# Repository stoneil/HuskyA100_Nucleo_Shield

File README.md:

Husky A100 Nucleo Shield
===

## Circuit

This board is for my MQP (Major Qualifying Project) to develop a autonomous robotic platform to compete in the Intelligent Ground Vehicle Competition. The purpose of this board is to provide a secure connection between the STM32F7 Nucleo microcontroller board, the Talon motor controllers (PWM) and the US Digital quadrature encoders. It breaks out power and I/O to all the connectors.

## PCB Layout
v1.0

v1.2

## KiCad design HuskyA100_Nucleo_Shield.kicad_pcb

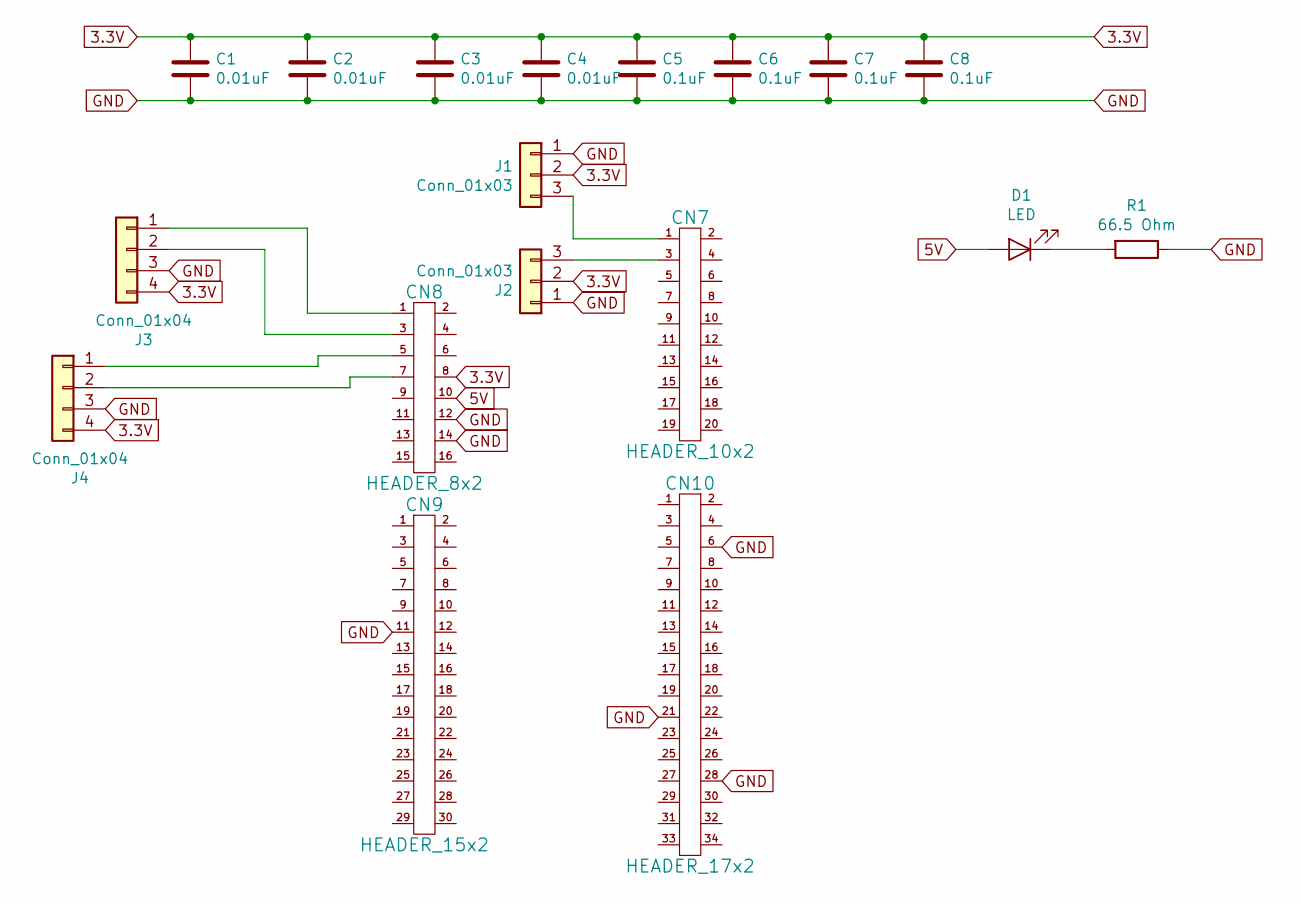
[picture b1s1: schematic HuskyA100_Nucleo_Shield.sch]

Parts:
C1, C2, C3, C4: 0.01uF; C_2220_5650Metric_Pad1.97x5.40mm_HandSolder
C5, C6, C7, C8: 0.1uF; C_2220_5650Metric_Pad1.97x5.40mm_HandSolder
CN7: HEADER_10x2; PinSocket_2x10_P2.54mm_Vertical
CN8: HEADER_8x2; PinSocket_2x08_P2.54mm_Vertical
CN9: HEADER_15x2; PinSocket_2x15_P2.54mm_Vertical
CN10: HEADER_17x2; PinSocket_2x17_P2.54mm_Vertical
D1: LED; LED_PLCC-2
J1, J2: Conn_01x03; Molex Mini-Lock Horizontal Header 3 circuit
J3, J4: Conn_01x04; Molex Mini-Lock Horizontal Header 4 circuit
R1: 66.5 Ohm; R_1206_3216Metric_Pad1.42x1.75mm_HandSolder

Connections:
3.3V: C1.1, C2.1, C3.1, C4.1, C5.1, C6.1, C7.1, C8.1, CN8.8, J1.2, J2.2, J3.4, J4.4
5V: CN8.10, D1.2 (A)
GND: C1.2, C2.2, C3.2, C4.2, C5.2, C6.2, C7.2, C8.2, CN8.12, CN8.14, CN9.11, CN10.6, CN10.21, CN10.28, J1.1, J2.1, J3.3, J4.3, R1.1
unnamed: CN7.1, J1.3
unnamed: CN7.3, J2.3
unnamed: CN8.1, J3.1
unnamed: CN8.3, J3.2
unnamed: CN8.5, J4.1
unnamed: CN8.7, J4.2
unnamed: D1.1 (K), R1.2

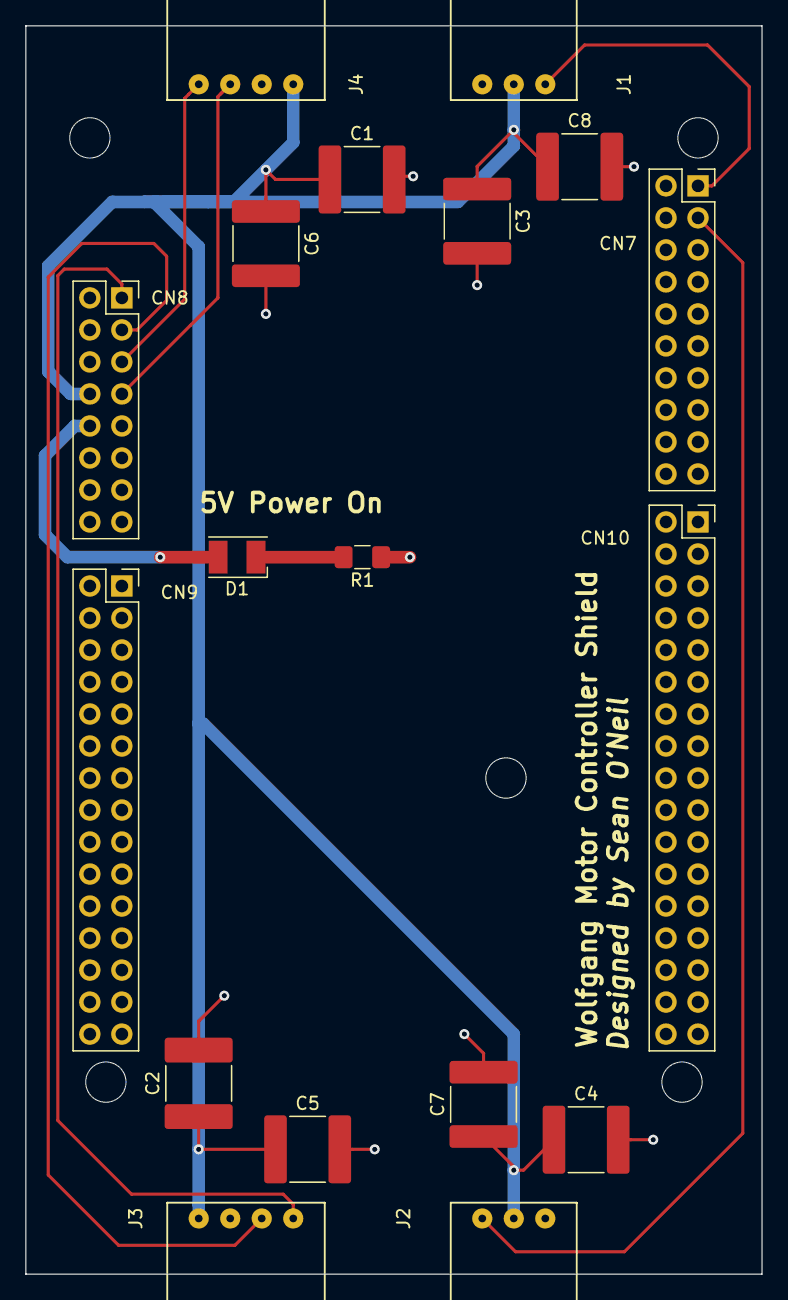
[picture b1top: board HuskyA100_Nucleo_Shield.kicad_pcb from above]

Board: 2 copper layers, 58.4 x 99.1 mm, 18 parts (0 on the bottom side), 10 nets.

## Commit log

2019-02-10 committing the first printed board version of the design and added a README
2019-02-13 rerouted the pins to be correct in the schematic + deleted old traces
2019-02-13 fixed header connector spacing and mounting hole placement
2019-02-13 Fixed #1 - enlargened Molex Connector pads for easier soldering. Last commit for this Issue
2019-02-13 Fixed #2 brought custom libraries I've been using into project repo and changed the symbol and footprint table URIs accordingly
2019-02-14 routed the traces
2019-02-15 Fixed #3 - replaced bypass caps with 5.6mm x 5.0mm case size to make them more easiy solderable
2019-02-15 Fix #4 - added power led and authorship. Also made the capacitor pads to 'hand-solderable' for easier assembly
2019-02-15 added a title, miscellaneous fixes changes
2019-02-15 plotted the gerbers for V2 and added soldermask clearance from DFM suggestions
2019-02-27 added gerbers that were sent for rev2
2019-04-08 added a pic of v1.2
